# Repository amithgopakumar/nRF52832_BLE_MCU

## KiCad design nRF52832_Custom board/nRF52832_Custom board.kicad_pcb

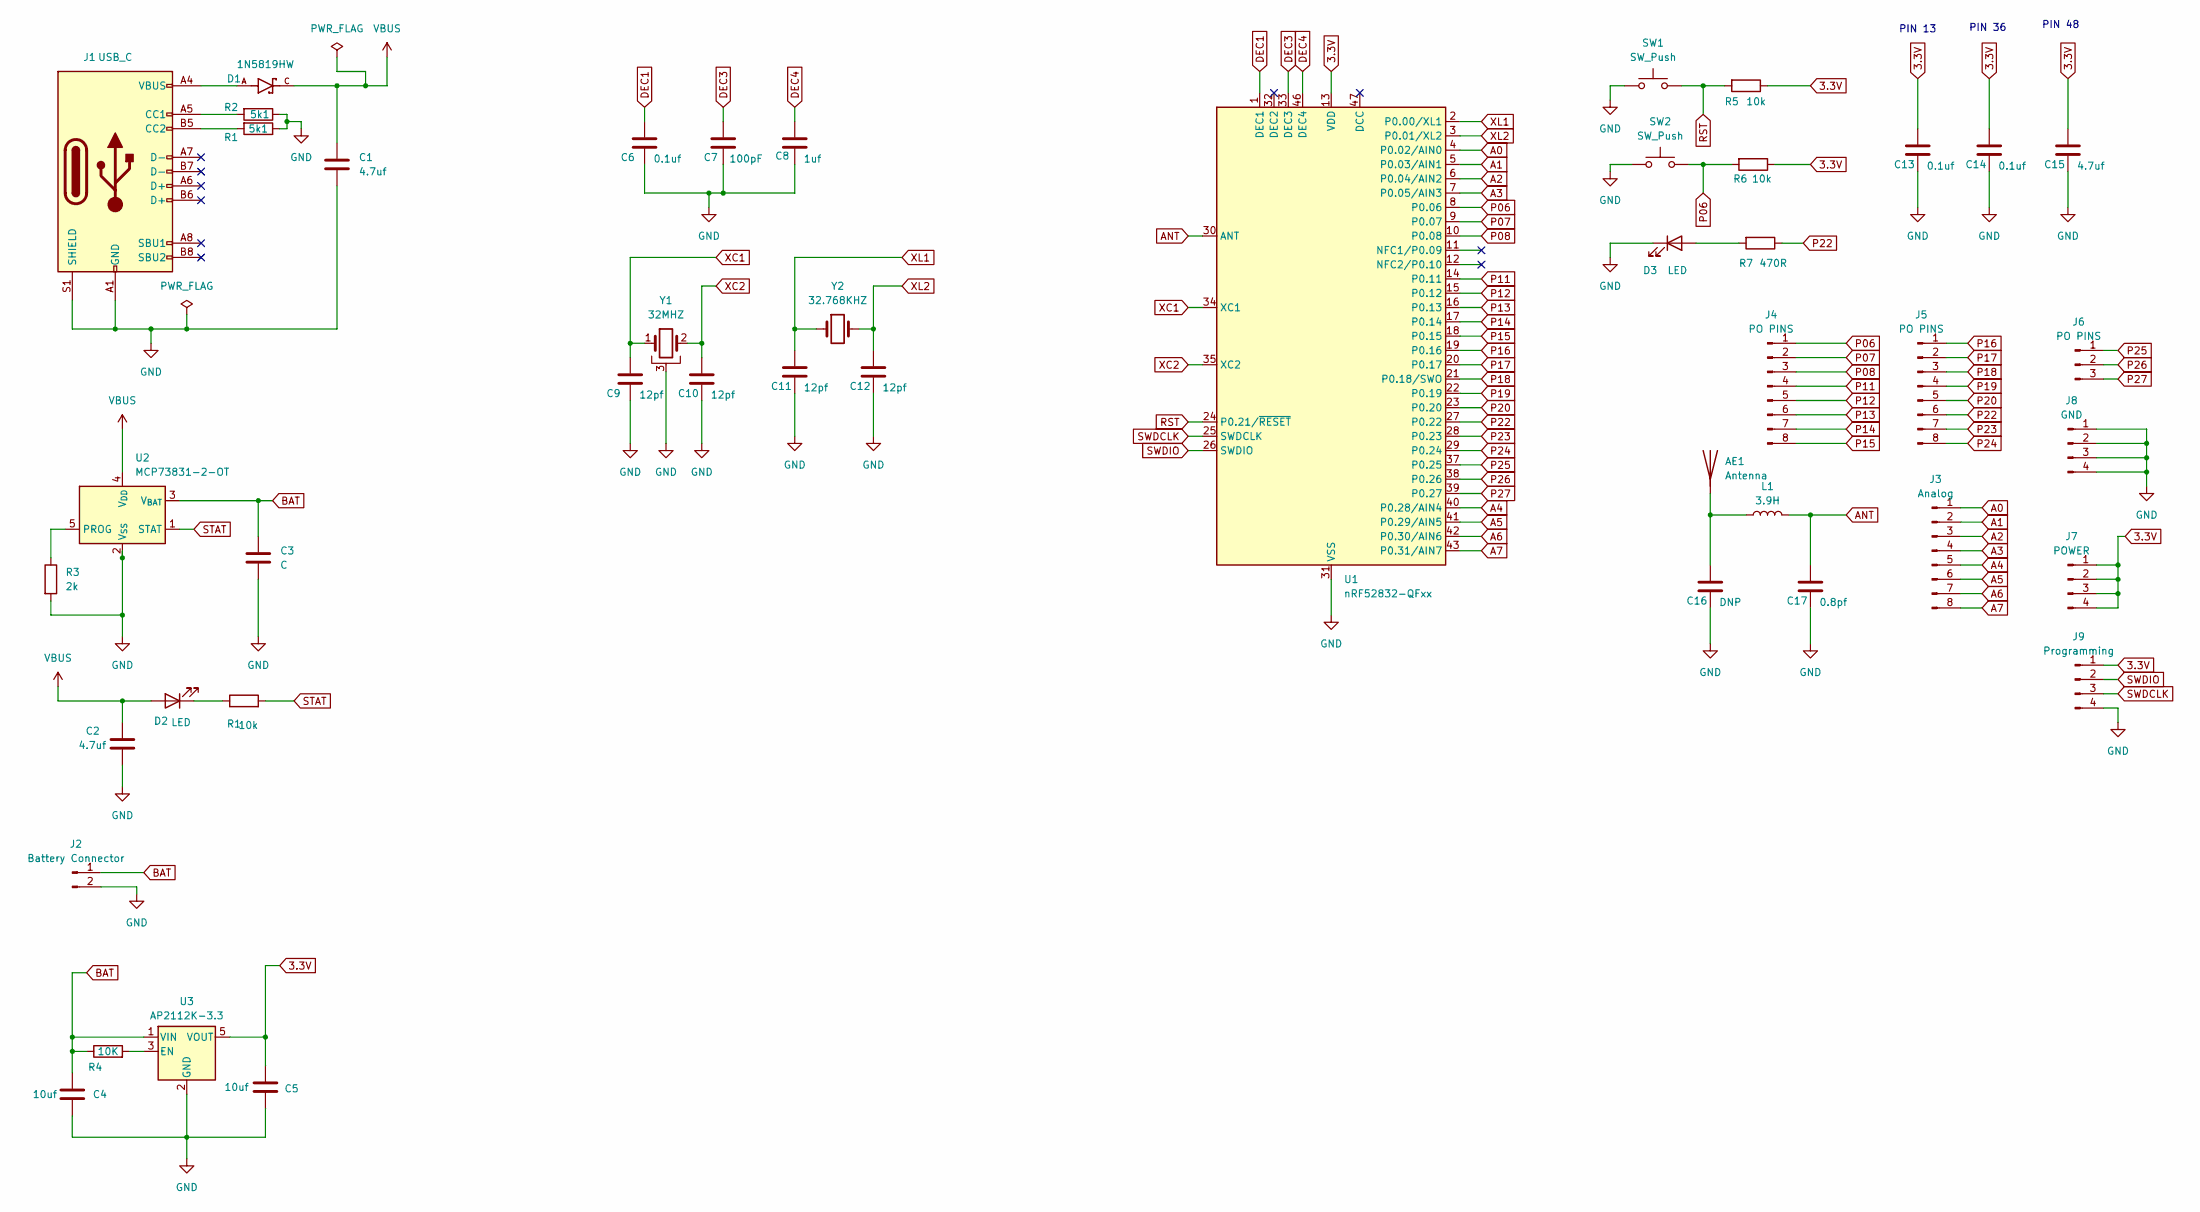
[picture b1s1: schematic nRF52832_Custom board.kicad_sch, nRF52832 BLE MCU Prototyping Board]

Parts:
5k1: R1; R_1206_3216Metric_Pad1.30x1.75mm_HandSolder
AE1: Antenna; Texas_SWRA117D_2.4GHz_Right
C1, C2, C15: 4.7uf; C_1206_3216Metric_Pad1.33x1.80mm_HandSolder
C3: C; C_1206_3216Metric_Pad1.33x1.80mm_HandSolder
C4, C5: 10uf; C_1206_3216Metric_Pad1.33x1.80mm_HandSolder
C6, C13, C14: 0.1uf; C_1206_3216Metric_Pad1.33x1.80mm_HandSolder
C7: 100pF; C_1206_3216Metric_Pad1.33x1.80mm_HandSolder
C8: 1uf; C_1206_3216Metric_Pad1.33x1.80mm_HandSolder
C9, C10, C11, C12: 12pf; C_1206_3216Metric_Pad1.33x1.80mm_HandSolder
C16: DNP; C_1206_3216Metric_Pad1.33x1.80mm_HandSolder
C17: 0.8pf; C_1206_3216Metric_Pad1.33x1.80mm_HandSolder
D1: 1N5819HW; SOD3715X145N; PARTREV 18-2
D2, D3: LED; LED_1206_3216Metric_Pad1.42x1.75mm_HandSolder
J1: USB_C; USB_C_Receptacle_GCT_USB4085
J2: Battery Connector; JST_XA_B02B-XASK-1_1x02_P2.50mm_Vertical
J3: Analog; JST_EH_B8B-EH-A_1x08_P2.50mm_Vertical
J4, J5: PO PINS; JST_EH_B8B-EH-A_1x08_P2.50mm_Vertical
J6: PO PINS; JST_EH_B3B-EH-A_1x03_P2.50mm_Vertical
J7: POWER; JST_EH_B4B-EH-A_1x04_P2.50mm_Vertical
J8: GND; JST_EH_B4B-EH-A_1x04_P2.50mm_Vertical
J9: Programming; JST_EH_B4B-EH-A_1x04_P2.50mm_Vertical
L1: 3.9H; L_1206_3216Metric_Pad1.22x1.90mm_HandSolder
R1, R5, R6: 10k; R_1206_3216Metric_Pad1.30x1.75mm_HandSolder
R2: 5k1; R_1206_3216Metric_Pad1.30x1.75mm_HandSolder
R3: 2k; R_1206_3216Metric_Pad1.30x1.75mm_HandSolder
R4: 10K; R_1206_3216Metric_Pad1.30x1.75mm_HandSolder
R7: 470R; R_1206_3216Metric_Pad1.30x1.75mm_HandSolder
SW1, SW2: SW_Push; SW_Tactile_SPST_NO_Straight_CK_PTS636Sx25SMTRLFS
U1: nRF52832-QFxx; QFN-48-1EP_6x6mm_P0.4mm_EP4.6x4.6mm
U2: MCP73831-2-OT; SOT-23-5_HandSoldering
U3: AP2112K-3.3; SOT-23-5_HandSoldering
Y1: 32MHZ; Oscillator_SMD_Abracon_ASE-4Pin_3.2x2.5mm_HandSoldering
Y2: 32.768KHZ; Crystal_SMD_3215-2Pin_3.2x1.5mm

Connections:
3.3V: C5.1, C13.1, C14.1, C15.1, J7.1, J7.2, J7.3, J7.4, J9.1, R5.1, R6.1, U1.13 (VDD), U1.36 (VDD), U1.48 (VDD), U3.5 (VOUT)
A0: J3.1, U1.4 (P0.02/AIN0)
A1: J3.2, U1.5 (P0.03/AIN1)
A2: J3.3, U1.6 (P0.04/AIN2)
A3: J3.4, U1.7 (P0.05/AIN3)
A4: J3.5, U1.40 (P0.28/AIN4)
A5: J3.6, U1.41 (P0.29/AIN5)
A6: J3.7, U1.42 (P0.30/AIN6)
A7: J3.8, U1.43 (P0.31/AIN7)
ANT: C17.1, L1.2, U1.30 (ANT)
BAT: C3.1, C4.1, J2.1, R4.1, U2.3 (V_{BAT}), U3.1 (VIN)
DEC1: C6.1, U1.1 (DEC1)
DEC3: C7.1, U1.33 (DEC3)
DEC4: C8.1, U1.46 (DEC4)
GND: 5k1.1, C1.2, C2.2, C3.2, C4.2, C5.2, C6.2, C7.2, C8.2, C9.2, C10.2, C11.2, C12.2, C13.2, C14.2, C15.2, C16.2, C17.2, D3.1 (K), J1.A1 (GND), J1.A12 (GND), J1.B1 (GND), J1.B12 (GND), J1.S1 (SHIELD), J2.2, J8.1, J8.2, J8.3, J8.4, J9.4, R2.1, R3.2, SW1.1, SW2.1, U1.31 (VSS), U1.45 (VSS), U1.49 (VSS), U2.2 (V_{SS}), U3.2 (GND), Y1.3
unnamed: AE1.1 (A), C16.1, L1.1
unnamed: D1.A, J1.A4 (VBUS), J1.A9 (VBUS), J1.B4 (VBUS), J1.B9 (VBUS)
unnamed: D2.1 (K), R1.1
unnamed: D3.2 (A), R7.2
unnamed: J1.A5 (CC1), R2.2
unnamed: 5k1.2, J1.B5 (CC2)
unnamed: R3.1, U2.5 (PROG)
unnamed: R4.2, U3.3 (EN)
P06: J4.1, R6.2, SW2.2, U1.8 (P0.06)
P07: J4.2, U1.9 (P0.07)
P08: J4.3, U1.10 (P0.08)
P11: J4.4, U1.14 (P0.11)
P12: J4.5, U1.15 (P0.12)
P13: J4.6, U1.16 (P0.13)
P14: J4.7, U1.17 (P0.14)
P15: J4.8, U1.18 (P0.15)
P16: J5.1, U1.19 (P0.16)
P17: J5.2, U1.20 (P0.17)
P18: J5.3, U1.21 (P0.18/SWO)
P19: J5.4, U1.22 (P0.19)
P20: J5.5, U1.23 (P0.20)
P22: J5.6, R7.1, U1.27 (P0.22)
P23: J5.7, U1.28 (P0.23)
P24: J5.8, U1.29 (P0.24)
P25: J6.1, U1.37 (P0.25)
P26: J6.2, U1.38 (P0.26)
P27: J6.3, U1.39 (P0.27)
RST: R5.2, SW1.2, U1.24 (P0.21/~RESET)
STAT: R1.2, U2.1 (STAT)
SWDCLK: J9.3, U1.25 (SWDCLK)
SWDIO: J9.2, U1.26 (SWDIO)
VBUS: C1.1, C2.1, D1.C, D2.2 (A), U2.4 (V_{DD})
XC1: C9.1, U1.34 (XC1), Y1.1
XC2: C10.1, U1.35 (XC2), Y1.2
XL1: C11.1, U1.2 (P0.00/XL1), Y2.1
XL2: C12.1, U1.3 (P0.01/XL2), Y2.2

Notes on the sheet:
PIN 36
PIN 13
PIN 48

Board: 2 copper layers, 46 parts (0 on the bottom side), 51 nets, no tracks yet.

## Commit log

2025-01-31 Foot Prints added
2025-01-31 Updated after errors in Crystal design
2025-01-31 VCC error Fixed
2025-01-31 JST connetectors added
2025-02-01 ERC errors Fixed
2025-02-02 Added Gitignore, Removed backups from git repo
2025-02-07 update i2C and SPI
2025-02-09 DRV,Antenna Foot Print
